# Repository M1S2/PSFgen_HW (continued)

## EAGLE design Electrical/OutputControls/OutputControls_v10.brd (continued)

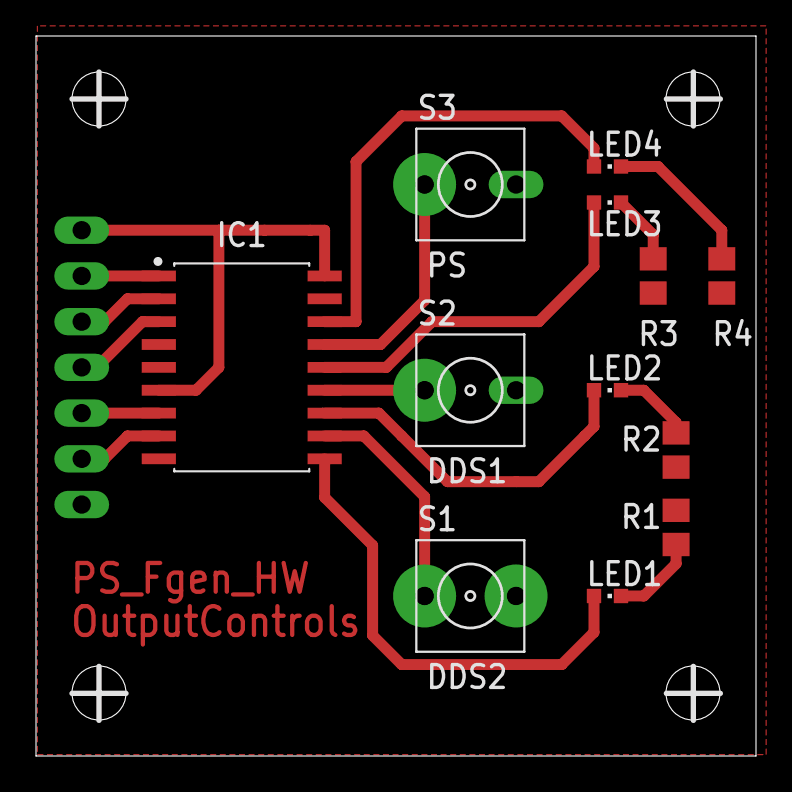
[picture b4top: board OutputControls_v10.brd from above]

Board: 2 copper layers, 40.0 x 40.0 mm, 13 parts (1 on the bottom side), 18 nets.

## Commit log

2021-06-01 Initial version under version control
2021-06-01 Board resized
2021-06-01 Resistors add to MainBoard to convert 5V to 3.3V for LCD signals
2021-06-03 Updated to new project name (PS_Fgen_HW), removed Z-Diode and ATX_PWR_ON signal from MainBoard
2021-06-03 MainBoard: Removed ATX_5V_SB input (combined VCC and +5V nets)
2021-06-03 Mechanical components exported as single .f3d files
2021-06-13 Images added and used in Readme
2021-07-05 Replaced Taste_komma by Taste_x1
2021-07-14 Added Schublade to housing to store cables etc.
2021-08-13 More images added and used in Readme
2021-08-14 Removed some Z-Diodes, removed Resistor R20 (PowerSupply, between OpAmp IC5B and transistors Q5 and Q6)
2021-08-29 Changed Resistor values of PowerSupply current measurement circuit (R21, R22, R23)
2021-09-02 Changed power stage of PowerSupply channel
2021-09-08 Removed Z-Diode D1 (PS_CUR), moved resistor R21 of current measurement circuit to be after this circuit
2021-12-01 Added cover for Schublade to housing
2022-01-05 Added Standfuss models
2022-04-26 Added DMMRectifier to Electrical folder
2022-04-28 Modified DMM circuit to use DMMRectifier PCB
2022-05-03 Adapted pilars of Seitenteil_rechts for DMMRectifier LEDs
2022-05-14 Added images of DMMRectifier to Readme
2024-09-03 Added OutputControls to Electrical folder
2025-01-15 Updated OutputControls and MainBoard in Electrical folder
2025-01-15 Updated FrontPanel and DMMRectifier in Electrical folder
2025-01-18 Updated all parts in Mechanical folder
2025-01-18 Updated documentation (images not updated yet)
2025-01-19 Updated documentation images
